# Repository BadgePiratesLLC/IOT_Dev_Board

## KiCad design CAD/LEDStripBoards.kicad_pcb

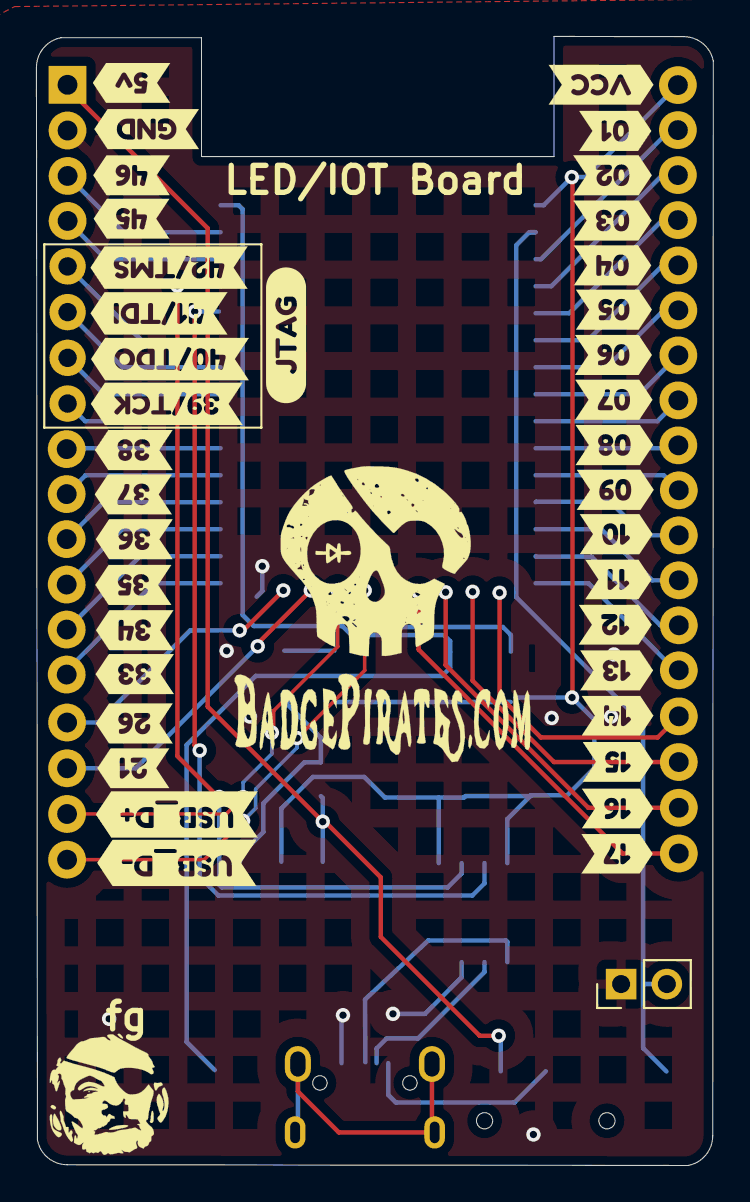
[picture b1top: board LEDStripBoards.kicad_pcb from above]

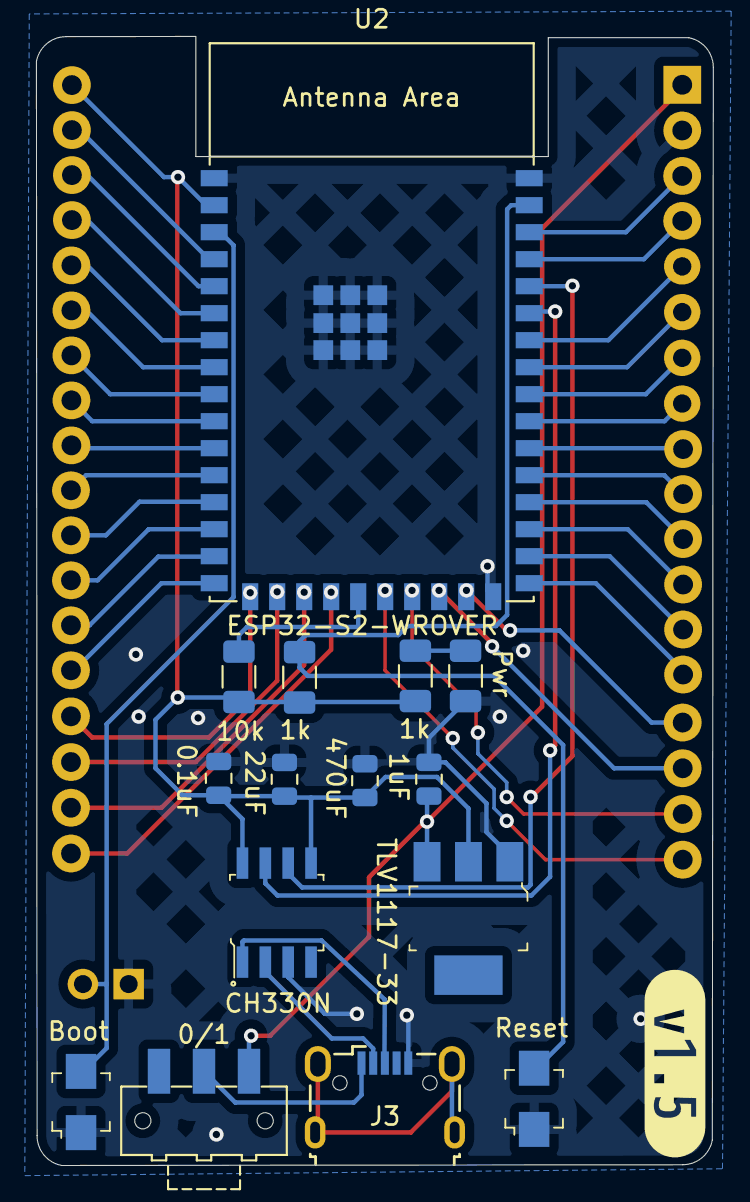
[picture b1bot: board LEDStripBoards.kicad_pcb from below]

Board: 2 copper layers, 37.6 x 62.7 mm, 64 parts (17 on the bottom side), 45 nets.

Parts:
0.1uF: 0.1uF; C_0805_2012Metric
0/1: 0/1; SW_SPDT_CK-JS102011SAQN
1k, 1k#2: 1k; R_1206_3216Metric
1uF: 1uF; C_0805_2012Metric
10k: 10k; R_1206_3216Metric
22uF: 22uF; C_0805_2012Metric
470uF: 470uF; C_0805_2012Metric
Boot: Boot_Btn; Switch_Tactile_SMD_B3U-1000P-BPVersion
CH330N: CH330N; SOIC-8-1EP_W3.9mm
J1, J11: Conn_01x02_Female; PinHeader_1x02_P2.54mm_Vertical
J2: JTAG; PinHeader_1x4_P2.54mm_Drill1.02mm
J3: USB_B_Mini; USB_Micro-B_Wuerth_629105150521
J4: Conn_01x04; PinHeader_1x4_P2.5mm_Drill1.1mm
J5, J6: Conn_01x05; PinHeader_1x5_P2.5mm_Drill1.1mm
J7: Conn_01x02; PinHeader_1x2_P2.5mm_Drill1.1mm
J8, J9: Conn_01x03; PinHeader_1x3_P2.5mm_Drill1.1mm
J10, J12: Conn_01x04_Female; PinHeader_1x04_P2.54mm_Vertical
Pwr: Pwr; R_1206_3216Metric
Reset: Reset_Btn; Switch_Tactile_SMD_B3U-1000P-BPVersion
TLV1117-33: TLV1117-33; SOT-223
U2: ESP32-S2-WROVER
kibuzzard-6268B5BC: G***; kibuzzard-6268B5BC
kibuzzard-6268B6A0: G***; kibuzzard-6268B6A0
kibuzzard-6268B6B8: G***; kibuzzard-6268B6B8
kibuzzard-6268B6C4: G***; kibuzzard-6268B6C4
kibuzzard-6268B6D1: G***; kibuzzard-6268B6D1
kibuzzard-6268B6DC: G***; kibuzzard-6268B6DC
kibuzzard-6268B6E6: G***; kibuzzard-6268B6E6
kibuzzard-6268B6F0: G***; kibuzzard-6268B6F0
kibuzzard-6268B6FB: G***; kibuzzard-6268B6FB
kibuzzard-6268B7B0: G***; kibuzzard-6268B7B0
kibuzzard-6268B8A3: G***; kibuzzard-6268B8A3
kibuzzard-6268B8B3: G***; kibuzzard-6268B8B3
kibuzzard-6268B9F3: G***; kibuzzard-6268B9F3
kibuzzard-6268B47B: G***; kibuzzard-6268B47B
kibuzzard-6268B63E: G***; kibuzzard-6268B63E
kibuzzard-6268B68E: G***; kibuzzard-6268B68E
kibuzzard-6268B75E: G***; kibuzzard-6268B75E
kibuzzard-6268B78D: G***; kibuzzard-6268B78D
kibuzzard-6268B79A: G***; kibuzzard-6268B79A
kibuzzard-6268B85C: G***; kibuzzard-6268B85C
kibuzzard-6268B612: G***; kibuzzard-6268B612
kibuzzard-6268B622: G***; kibuzzard-6268B622
kibuzzard-6268B659: G***; kibuzzard-6268B659
kibuzzard-6268B673: G***; kibuzzard-6268B673
kibuzzard-6268B680: G***; kibuzzard-6268B680
kibuzzard-6268B705: G***; kibuzzard-6268B705
kibuzzard-6268B781: G***; kibuzzard-6268B781
kibuzzard-6268B841: G***; kibuzzard-6268B841
kibuzzard-6268B850: G***; kibuzzard-6268B850
kibuzzard-6268B865: G***; kibuzzard-6268B865
kibuzzard-6268B874: G***; kibuzzard-6268B874
kibuzzard-6268B895: G***; kibuzzard-6268B895
kibuzzard-6268BA2C: G***; kibuzzard-6268BA2C
kibuzzard-6268BA03: G***; kibuzzard-6268BA03
kibuzzard-6268BA3D: G***; kibuzzard-6268BA3D
kibuzzard-6268BA4E: G***; kibuzzard-6268BA4E
kibuzzard-6268BA5F: G***; kibuzzard-6268BA5F
kibuzzard-6268BA9E: G***; kibuzzard-6268BA9E

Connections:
+5V: 0/1.2 (B), J3.1 (VBUS)
Boot: Boot.2 (D), J11.2, U2.3 (IO00)
D+: CH330N.1 (UD+), J3.3 (D+)
D-: CH330N.2 (UD-), J3.2 (D-)
GND: 0.1uF.2, 1uF.2, 22uF.2, 470uF.2, Boot.1 (C), CH330N.3 (GND), J1.2, J3.5 (GND), J11.1, Pwr.1 (K), Reset.1 (C), TLV1117-33.1 (GND), U2.1 (GND), U2.26 (GND), U2.42 (GND), U2.43 (GND)
IO01: J4.2, U2.4 (IO01)
IO02: J4.3, U2.5 (IO02)
IO03: J4.4, U2.6 (IO03)
IO04: J5.1, U2.7 (IO04)
IO05: J5.2, U2.8 (IO05)
IO06: J5.3, U2.9 (IO06)
IO07: J5.4, U2.10 (IO07)
IO08: J5.5, U2.11 (IO08)
IO09: J6.1, U2.12 (IO09)
IO10: J6.2, U2.13 (IO10)
IO11: J6.3, U2.14 (IO11)
IO12: J6.4, U2.15 (IO12)
IO13: J6.5, U2.16 (IO13)
IO14: J10.1, U2.17 (IO14)
IO15: J10.2, U2.18 (IO15)
IO16: J10.3, U2.19 (IO16)
IO17: J10.4, U2.20 (IO17)
IO21: J12.2, U2.24 (IO21)
IO26: J12.1, U2.25 (IO26)
IO33: J9.3, U2.27 (IO33)
IO34: J9.2, U2.28 (IO34)
IO35: J9.1, U2.29 (IO35)
IO36: J8.3, U2.30 (IO36)
IO37: J8.2, U2.31 (IO37)
IO38: J8.1, U2.32 (IO38)
IO39: J2.4, U2.33 (IO39)
IO40: J2.3, U2.34 (IO40)
IO41: J2.2, U2.35 (IO41)
IO42: J2.1, U2.36 (IO42)
IO45: J7.2, U2.39 (IO45)
IO46: J7.1, U2.40 (IO46)
unnamed: 1k.2, Pwr.2 (A)
unnamed: 10k.1, U2.21 (IO18)
RESET: 1k#2.2, Reset.2 (D), U2.41 (EN)
USB_D+: J12.3, U2.23 (USB_D+)
USB_D-: J12.4, U2.22 (USB_D-)
USB_RX_ESP_TX: CH330N.7 (RXD), U2.37 (TXD0)
USB_TX_ESP_RX: CH330N.6 (TXD), U2.38 (RXD0)
VBUS: 0/1.3 (C), 1uF.1, J1.1, TLV1117-33.3 (VI)
VCC: 0.1uF.1, 1k.1, 1k#2.1, 10k.2, 22uF.1, 470uF.1, CH330N.5 (VCC), CH330N.8 (V3), J4.1, TLV1117-33.2 (VO), U2.2 (3V3)

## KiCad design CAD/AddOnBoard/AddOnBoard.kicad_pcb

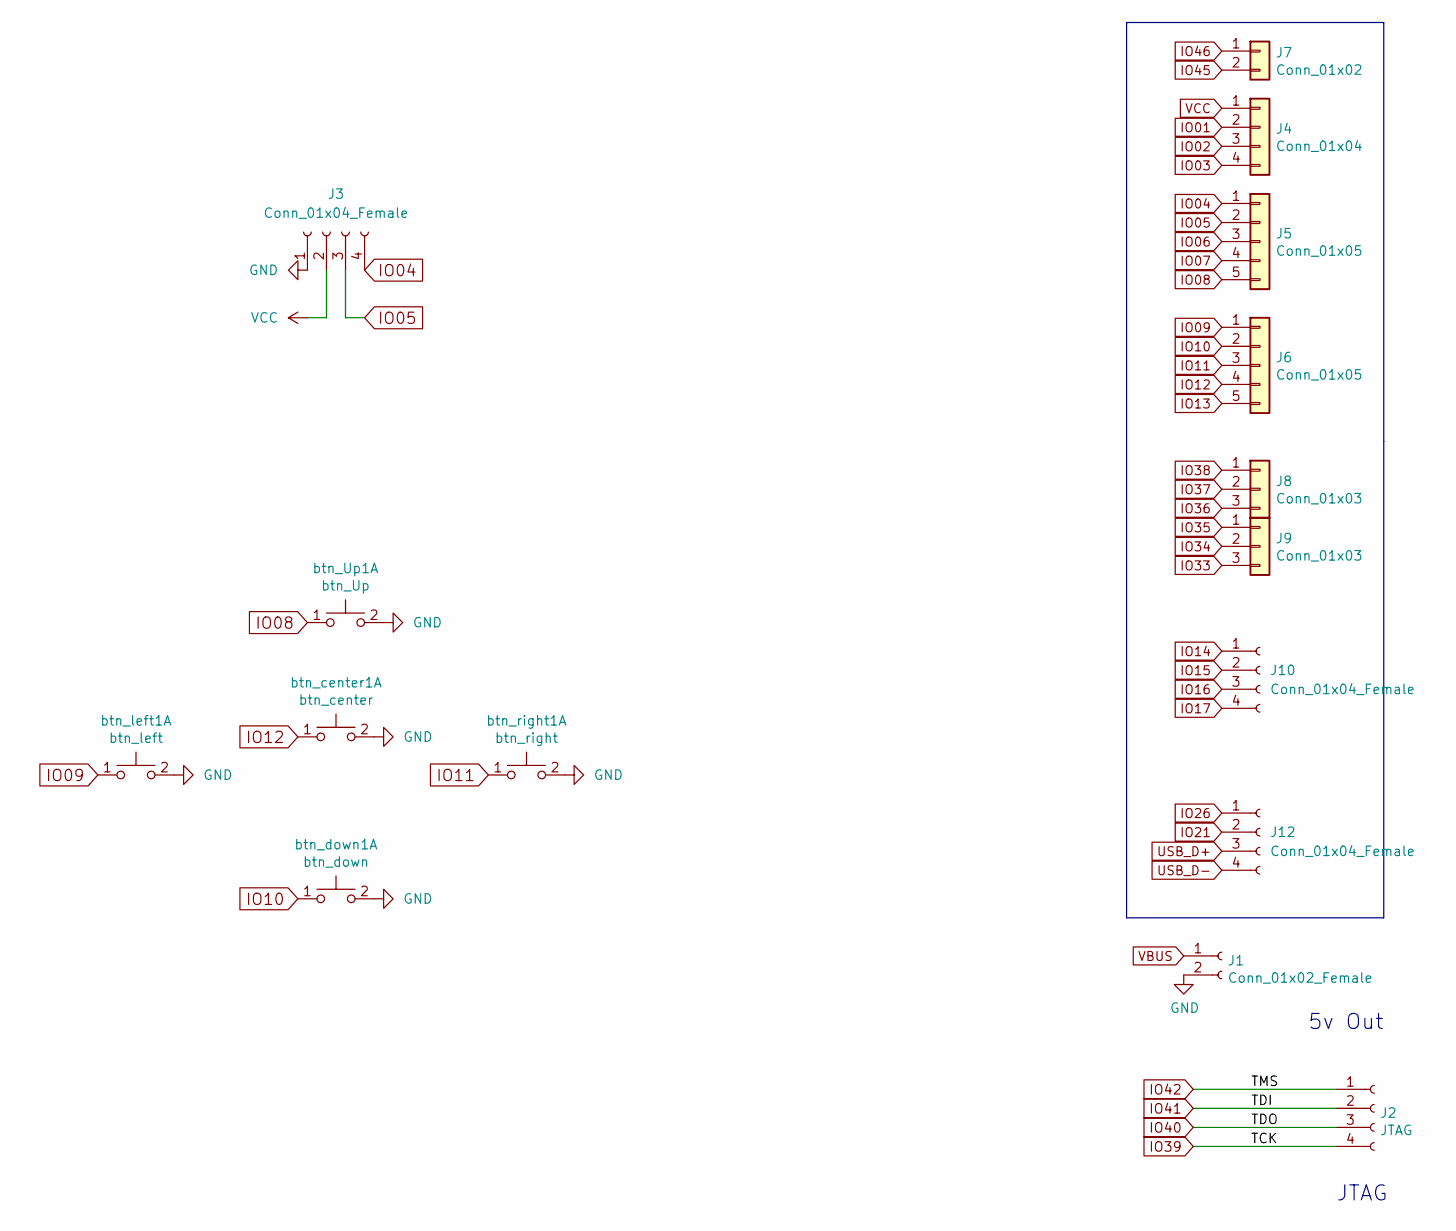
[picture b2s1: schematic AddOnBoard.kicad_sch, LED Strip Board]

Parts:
J1: Conn_01x02_Female; PinHeader_1x02_P2.54mm_Vertical
J2: JTAG; PinHeader_1x4_P2.54mm_Drill1.02mm
J3, J10, J12: Conn_01x04_Female; PinHeader_1x04_P2.54mm_Vertical
J4: Conn_01x04; PinHeader_1x4_P2.5mm_Drill1.1mm
J5, J6: Conn_01x05; PinHeader_1x5_P2.5mm_Drill1.1mm
J7: Conn_01x02; PinHeader_1x2_P2.5mm_Drill1.1mm
J8, J9: Conn_01x03; PinHeader_1x3_P2.5mm_Drill1.1mm
btn_Up1: btn_Up; Switch_Tactile_SMD_B3U-1000P-BPVersion
btn_center1: btn_center; Switch_Tactile_SMD_B3U-1000P-BPVersion
btn_down1: btn_down; Switch_Tactile_SMD_B3U-1000P-BPVersion
btn_left1: btn_left; Switch_Tactile_SMD_B3U-1000P-BPVersion
btn_right1: btn_right; Switch_Tactile_SMD_B3U-1000P-BPVersion

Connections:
GND: J1.2, J3.1, btn_Up1.2 (D), btn_center1.2 (D), btn_down1.2 (D), btn_left1.2 (D), btn_right1.2 (D)
IO01: J4.2
IO02: J4.3
IO03: J4.4
IO04: J3.4, J5.1
IO05: J3.3, J5.2
IO06: J5.3
IO07: J5.4
IO08: J5.5, btn_Up1.1 (C)
IO09: J6.1, btn_left1.1 (C)
IO10: J6.2, btn_down1.1 (C)
IO11: J6.3, btn_right1.1 (C)
IO12: J6.4, btn_center1.1 (C)
IO13: J6.5
IO14: J10.1
IO15: J10.2
IO16: J10.3
IO17: J10.4
IO21: J12.2
IO26: J12.1
IO33: J9.3
IO34: J9.2
IO35: J9.1
IO36: J8.3
IO37: J8.2
IO38: J8.1
IO39: J2.4
IO40: J2.3
IO41: J2.2
IO42: J2.1
IO45: J7.2
IO46: J7.1
USB_D+: J12.3
USB_D-: J12.4
VBUS: J1.1
VCC: J3.2, J4.1

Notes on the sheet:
JTAG
5v Out

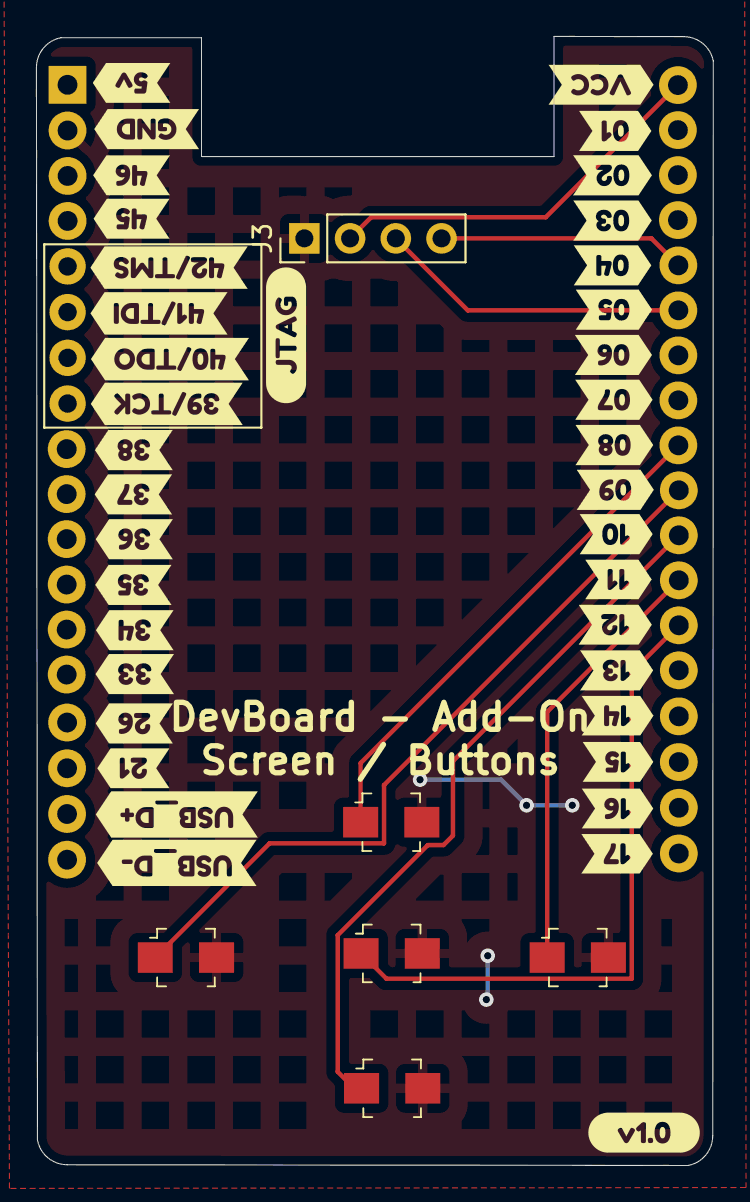
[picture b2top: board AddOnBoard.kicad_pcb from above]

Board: 2 copper layers, 37.6 x 62.7 mm, 54 parts (1 on the bottom side), 9 nets.

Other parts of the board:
kibuzzard-626A8FA0: G***; kibuzzard-626A8FA0
kibuzzard-6268B5BC: G***; kibuzzard-6268B5BC
kibuzzard-6268B6A0: G***; kibuzzard-6268B6A0
kibuzzard-6268B6B8: G***; kibuzzard-6268B6B8
kibuzzard-6268B6C4: G***; kibuzzard-6268B6C4
kibuzzard-6268B6D1: G***; kibuzzard-6268B6D1
kibuzzard-6268B6DC: G***; kibuzzard-6268B6DC
kibuzzard-6268B6E6: G***; kibuzzard-6268B6E6
kibuzzard-6268B6F0: G***; kibuzzard-6268B6F0
kibuzzard-6268B6FB: G***; kibuzzard-6268B6FB
kibuzzard-6268B7B0: G***; kibuzzard-6268B7B0
kibuzzard-6268B8A3: G***; kibuzzard-6268B8A3
kibuzzard-6268B8B3: G***; kibuzzard-6268B8B3
kibuzzard-6268B9F3: G***; kibuzzard-6268B9F3
kibuzzard-6268B63E: G***; kibuzzard-6268B63E
kibuzzard-6268B68E: G***; kibuzzard-6268B68E
kibuzzard-6268B75E: G***; kibuzzard-6268B75E
kibuzzard-6268B78D: G***; kibuzzard-6268B78D
kibuzzard-6268B79A: G***; kibuzzard-6268B79A
kibuzzard-6268B85C: G***; kibuzzard-6268B85C
kibuzzard-6268B612: G***; kibuzzard-6268B612
kibuzzard-6268B622: G***; kibuzzard-6268B622
kibuzzard-6268B659: G***; kibuzzard-6268B659
kibuzzard-6268B673: G***; kibuzzard-6268B673
kibuzzard-6268B680: G***; kibuzzard-6268B680
kibuzzard-6268B705: G***; kibuzzard-6268B705
kibuzzard-6268B781: G***; kibuzzard-6268B781
kibuzzard-6268B841: G***; kibuzzard-6268B841
kibuzzard-6268B850: G***; kibuzzard-6268B850
kibuzzard-6268B865: G***; kibuzzard-6268B865
kibuzzard-6268B874: G***; kibuzzard-6268B874
kibuzzard-6268B895: G***; kibuzzard-6268B895
kibuzzard-6268BA2C: G***; kibuzzard-6268BA2C
kibuzzard-6268BA03: G***; kibuzzard-6268BA03
kibuzzard-6268BA3D: G***; kibuzzard-6268BA3D
kibuzzard-6268BA4E: G***; kibuzzard-6268BA4E
kibuzzard-6268BA5F: G***; kibuzzard-6268BA5F
kibuzzard-6268BA9E: G***; kibuzzard-6268BA9E

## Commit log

2022-05-25 Upload of Files
2022-08-31 code update
2022-11-27 Adding Templates
